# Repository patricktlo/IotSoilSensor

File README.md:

# IotSoilSensor

## This document is under construction!

This project aims to create a cheap LoRa-connected device to measure soil moisture using an embedded capacitive sensor. It also has a temperature sensor (NTC) and an air humidity sensor (HR202).

This project also contains a small simple gateway for LoRa using a LoRa module, a microcontroller and a Raspberry Pi.

## Soil moisture sensor

For the geometry of the sensor I chose a fringing field capacitive sensor because it is well documented and used in academic papers, it was also easy to design it in KiCAD, and easy to simulate in FEMM.

To measure the capacitance a simple RC circuit is used, where R is chosen to achieve a good resolution and measuring range. A comparator (which is inside the STM32L051 microcontroller) is connected to the output of the RC circuit, a simple resistive divider giving Vcc/2 is connected to the other pin of the comparator. 

A square wave is applied to the RC circuit, once the comparator changes state, the code of the MCU gets the value of the timer (the same one used for the square wave generations), with this value it is possible to measure the RC constant and hence the capacitive value. This circuit works quite well, before testing the capacitive sensor with it I tried it with capacitors and the results were really close to the nominal capacitive values ([data here](1_Simulations/Moisture%20sensor/Calibration/test_caps.ods))

### Soil moisture sensor calibration

The gravimetric analysis was used to calibrate our sensor, data can be found [here](1_Simulations/Moisture%20sensor/Calibration/test_gravi.ods). 

## Temperature sensor
The temperature sensor is an NTC thermistor because it's simple, cheap and doesn't depend on battery voltage (like DHT11 and others). The circuit is a simple resistor divider, where the value of the other resistor was chosen by finding the inflection point (using a double derivative, more information on the [HR202 sensor python notebook](1_Simulations/HR202/RH Simulation.ipynb), where I developed the math), you can find the math and some cool graphs on the [NTC sensor python notebook](1_Simulations/NTC/Simulation.ipynb). 

### Temperature sensor calibration
I used the beta-equation for the NTC, [look here for more info](1_Simulations/NTC/Simulation.ipynb).
      
The value of beta was given in the datasheet but I wanted to get a closer value so I calibrated it, see more details [in this spreadsheet](1_Simulations/NTC/NTC_calibration.ods).

## Air humidity sensor
The air humidity sensor was a tough one, it would've been pretty simple and straightforward to use a DHT11, but it would stop working when battery levels got to 3V (so pretty soon considering I'm using two AA batteries). So, I chose the HR202, there's not much about it but it's basically a resistive sensor, the RH value changes with temperature and you have to apply AC to it.

In order to provide AC voltage, I polarized the output at Vcc/2, using a resistor divider (look into the [LTSpice file](1_Simulations/HR202/hr202.asc) or the [KiCAD schematic](2_PCB/schematic.pdf) for more. The value of the resistor in this resistor divider is crucial because its value (or more precisely, the equivalent value of the two) define the output characteristics. To find the value of the resistors the inflex point was used (more info on the [HR202 sensor python notebook](1_Simulations/HR202/RH%20Simulation.ipynb)).

Also, just a quick note, since the input voltage is a square wave controlled by a timer, and we want to gather data from the ADC in sync with the square wave, it is needed to fire the ADC conversion with a timer as well.

### Air humidity calibration

It is difficult to calibrate this sensor, I found that the values in the datasheet weren't close to my results (although it could be some error in the circuit, I later found in another datasheet a somewhat different circuit which could work better). In order to get a fixed relative air humidity, I put the sensor inside a sealed container with a bottle cap of salt and water, that way after a few hours it gets to 75%.
I had an air humidity sensor so I could also use it as a reference. Even though the HR202 wasn't giving out exactly what was written on the datasheet, one could see the output voltage had a correlation with the humidity, so I got two known points, the 75% from the salt-water solution and the ambient RH from the other sensor, and fitted my sensor values to this line. It's far from perfect but it does give an idea of the RH.

## Battery

## LoRa

## STM32L051

## PCB

## Gateway
### Database

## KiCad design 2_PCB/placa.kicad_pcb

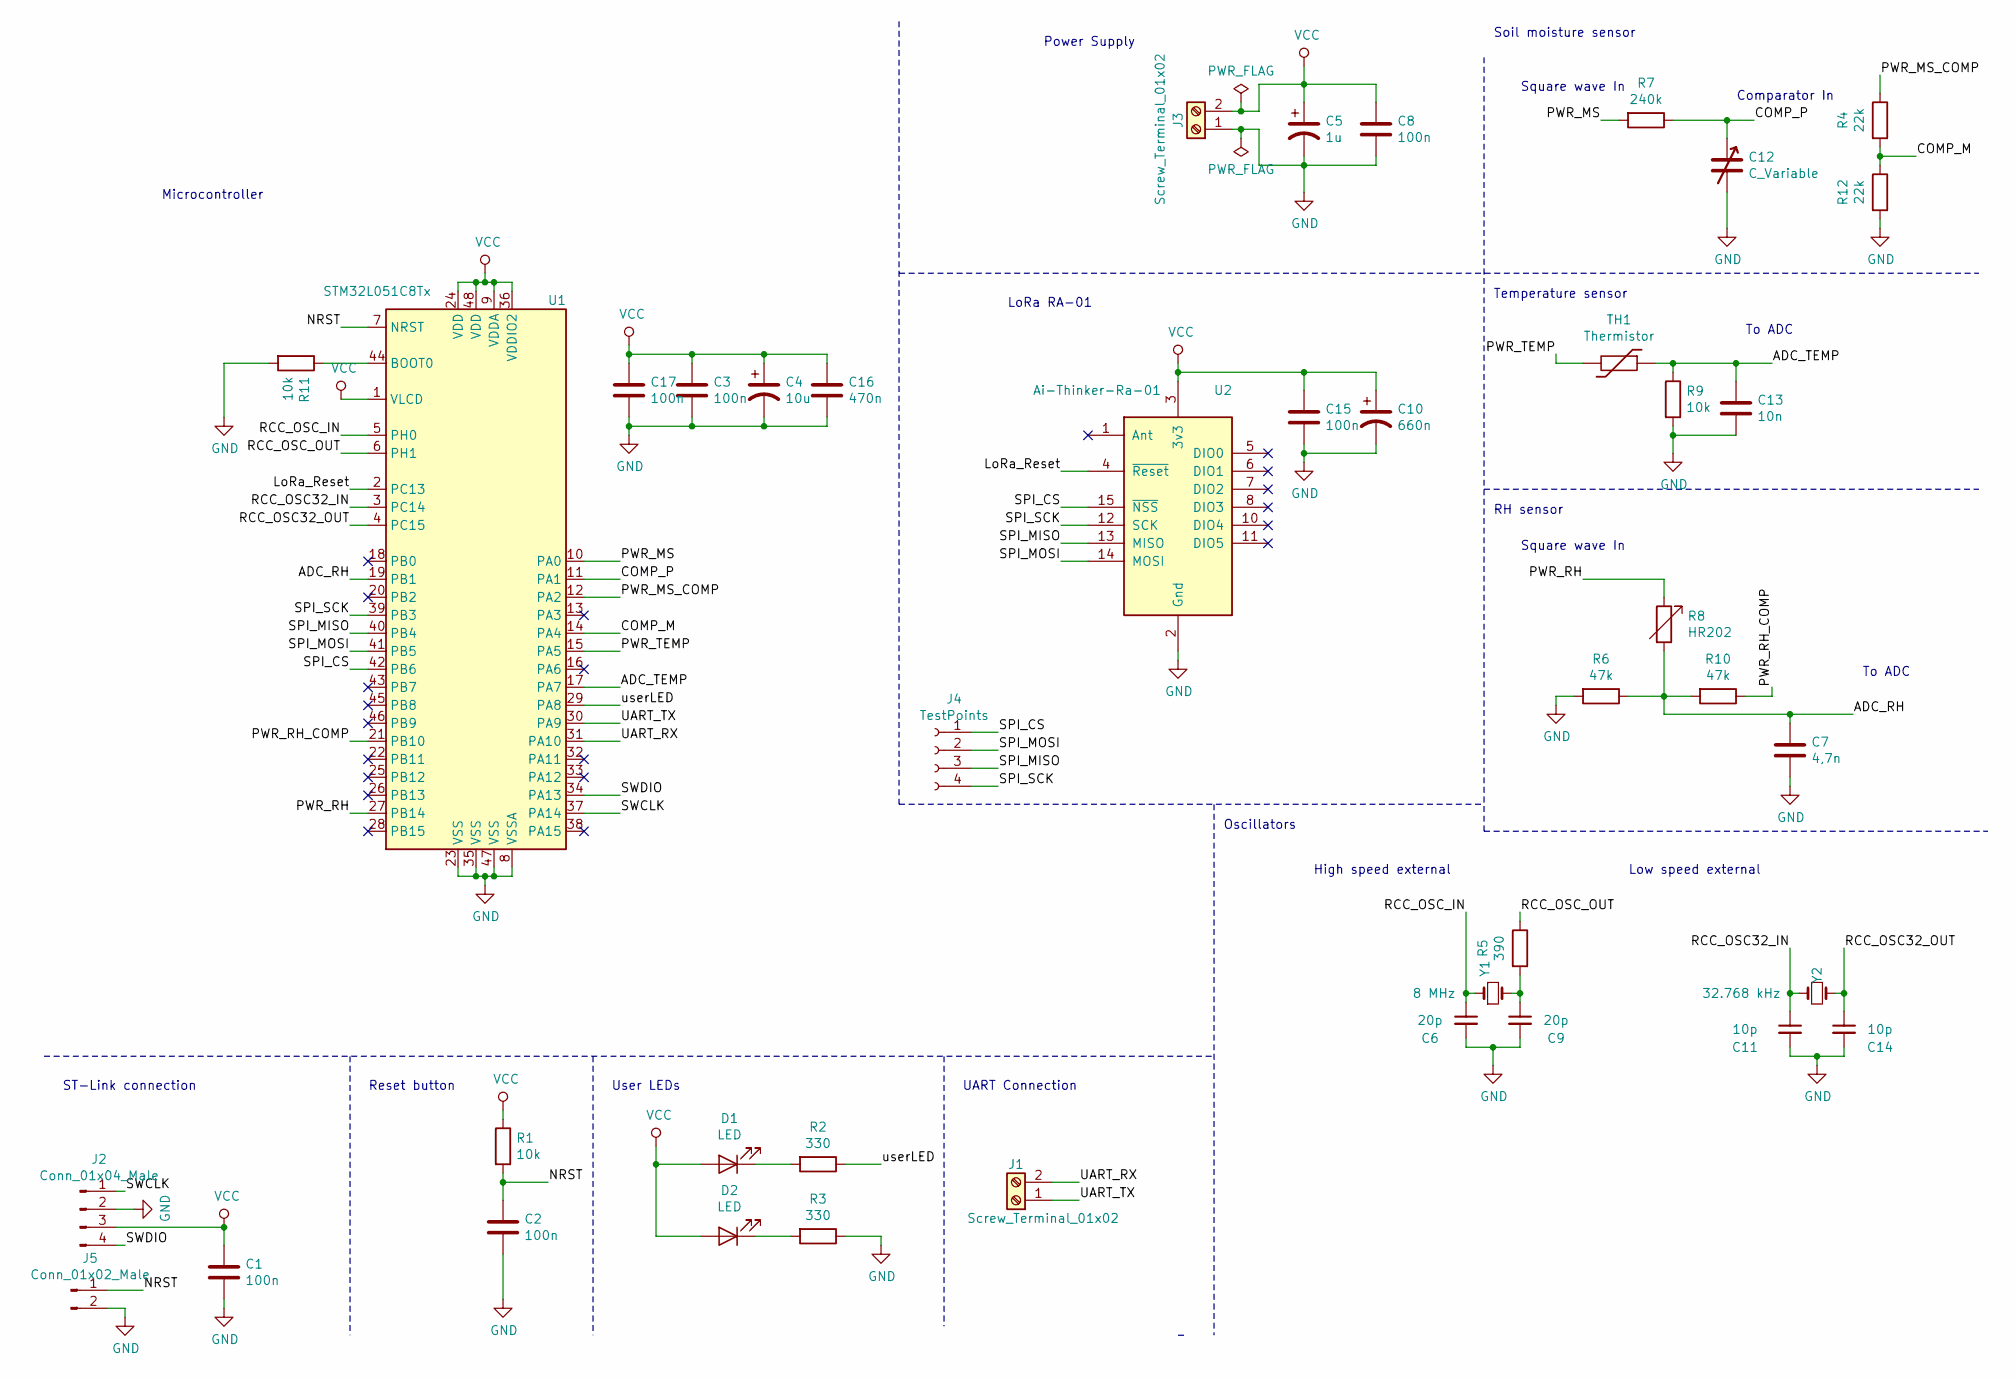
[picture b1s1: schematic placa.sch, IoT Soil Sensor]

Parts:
C1, C2, C3, C8, C15, C17: 100n; C_0805_2012Metric_Pad1.15x1.40mm_HandSolder
C4: 10u; CP_Radial_D5.0mm_P2.50mm
C5: 1u; CP_Radial_D5.0mm_P2.00mm
C6, C9: 20p; C_0805_2012Metric_Pad1.15x1.40mm_HandSolder
C7: 4,7n; C_0805_2012Metric_Pad1.15x1.40mm_HandSolder
C10: 660n; C_0805_2012Metric_Pad1.15x1.40mm_HandSolder
C11, C14: 10p; C_0805_2012Metric_Pad1.15x1.40mm_HandSolder
C12: C_Variable; Moisture Sensor
C13: 10n; C_0805_2012Metric_Pad1.15x1.40mm_HandSolder
C16: 470n; C_0805_2012Metric_Pad1.15x1.40mm_HandSolder
D1, D2: LED; LED_0805_2012Metric_Pad1.15x1.40mm_HandSolder
J1, J3: Screw_Terminal_01x02; PinHeader_1x02_P2.54mm_Vertical
J2: Conn_01x04_Male; PinHeader_1x04_P2.54mm_Vertical
J4: TestPoints; PinHeader_1x04_P2.54mm_Vertical
J5: Conn_01x02_Male; PinHeader_1x02_P2.54mm_Vertical
R1, R9, R11: 10k; R_0805_2012Metric_Pad1.15x1.40mm_HandSolder
R2, R3: 330; R_0805_2012Metric_Pad1.15x1.40mm_HandSolder
R4, R12: 22k; R_0805_2012Metric_Pad1.15x1.40mm_HandSolder
R5: 390; R_0805_2012Metric_Pad1.15x1.40mm_HandSolder
R6, R10: 47k; R_0805_2012Metric_Pad1.15x1.40mm_HandSolder
R7: 240k; R_0805_2012Metric_Pad1.15x1.40mm_HandSolder
R8: HR202; R_Axial_DIN0204_L3.6mm_D1.6mm_P1.90mm_Vertical
TH1: Thermistor; R_Axial_DIN0204_L3.6mm_D1.6mm_P1.90mm_Vertical
U1: STM32L051C8Tx; LQFP-48_7x7mm_P0.5mm
U2: Ai-Thinker-Ra-01; Ai-Thinker-Ra-01-LoRa
Y1: 8 MHz; Crystal_HC49-U_Vertical
Y2: 32.768 kHz; Crystal_Round_D1.0mm_Vertical

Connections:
/ADC_RH: C7.1, R6.1, R8.2, R10.2, U1.19 (PB1)
/ADC_TEMP: C13.1, R9.1, TH1.1, U1.17 (PA7)
/COMP_M: R4.2, R12.1, U1.14 (PA4)
/COMP_P: C12.1, R7.1, U1.11 (PA1)
/LoRa_Reset: U1.2 (PC13), U2.4 (~Reset)
/NRST: C2.1, J5.1, R1.2, U1.7 (NRST)
/PWR_MS: R7.2, U1.10 (PA0)
/PWR_MS_COMP: R4.1, U1.12 (PA2)
/PWR_RH: R8.1, U1.27 (PB14)
/PWR_RH_COMP: R10.1, U1.21 (PB10)
/PWR_TEMP: TH1.2, U1.15 (PA5)
/RCC_OSC32_IN: C11.1, U1.3 (PC14), Y2.2
/RCC_OSC32_OUT: C14.1, U1.4 (PC15), Y2.1
/RCC_OSC_IN: C6.1, U1.5 (PH0), Y1.1
/RCC_OSC_OUT: R5.1, U1.6 (PH1)
/SPI_CS: J4.1, U1.42 (PB6), U2.15 (~NSS)
/SPI_MISO: J4.3, U1.40 (PB4), U2.13 (MISO)
/SPI_MOSI: J4.2, U1.41 (PB5), U2.14 (MOSI)
/SPI_SCK: J4.4, U1.39 (PB3), U2.12 (SCK)
/SWCLK: J2.1, U1.37 (PA14)
/SWDIO: J2.4, U1.34 (PA13)
/UART_RX: J1.2, U1.31 (PA10)
/UART_TX: J1.1, U1.30 (PA9)
/userLED: R2.1, U1.29 (PA8)
GND: C1.2, C2.2, C3.2, C4.2, C5.2, C6.2, C7.2, C8.2, C9.2, C10.2, C11.2, C12.2, C13.2, C14.2, C15.2, C16.2, C17.2, J2.2, J3.1, J5.2, R3.1, R6.2, R9.2, R11.2, R12.2, U1.8 (VSSA), U1.23 (VSS), U1.35 (VSS), U1.47 (VSS), U2.2 (Gnd), U2.9 (Gnd), U2.16 (Gnd)
unnamed: C9.1, R5.2, Y1.2
unnamed: D1.1 (K), R2.2
unnamed: D2.1 (K), R3.2
unnamed: R11.1, U1.44 (BOOT0)
VCC: C1.1, C3.1, C4.1, C5.1, C8.1, C10.1, C15.1, C16.1, C17.1, D1.2 (A), D2.2 (A), J2.3, J3.2, R1.1, U1.1 (VLCD), U1.9 (VDDA), U1.24 (VDD), U1.36 (VDDIO2), U1.48 (VDD), U2.3 (3v3)

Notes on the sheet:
Square wave In
Comparator In
Soil moisture sensor
Temperature sensor
RH sensor
To ADC
Power Supply
ST-Link connection
Reset button
User LEDs
Oscillators
High speed external
Low speed external
UART Connection
LoRa RA-01
Microcontroller

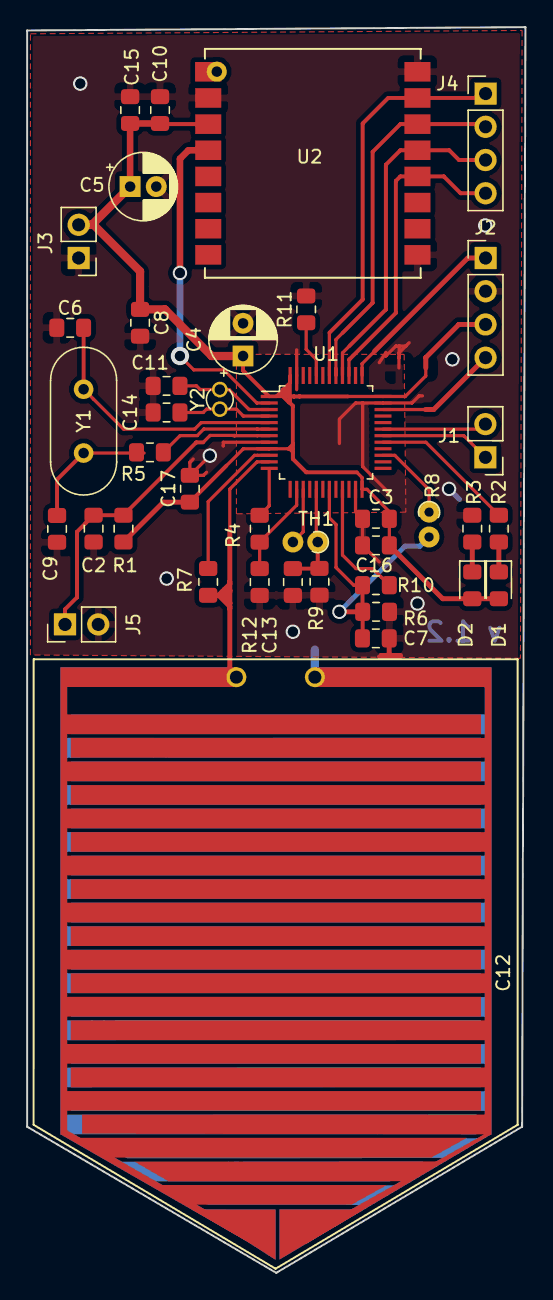
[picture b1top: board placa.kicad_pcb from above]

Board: 2 copper layers, 38.1 x 95.2 mm, 40 parts (0 on the bottom side), 30 nets.

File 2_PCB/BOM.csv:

"Id";"Designator";"Package";"Quantity";"Designation";"Supplier and ref";
1;"C12";"Moisture Sensor";1;"C_Variable";;;
2;"U2";"Ai-Thinker-Ra-01-LoRa";1;"Ai-Thinker-Ra-01";;;
3;"U1";"LQFP-48_7x7mm_P0.5mm";1;"STM32L051C8Tx";;;
4;"C16";"C_0805_2012Metric_Pad1.15x1.40mm_HandSolder";1;"470n";;;
5;"Y2";"Crystal_Round_D1.0mm_Vertical";1;"32.768 kHz";;;
6;"TH1";"R_Axial_DIN0204_L3.6mm_D1.6mm_P1.90mm_Vertical";1;"Thermistor";;;
7;"C1,C2,C3,C8,C15";"C_0805_2012Metric_Pad1.15x1.40mm_HandSolder";5;"100n";;;
8;"C4";"CP_Radial_D5.0mm_P2.50mm";1;"10u";;;
9;"C5";"CP_Radial_D5.0mm_P2.00mm";1;"1u";;;
10;"C6,C9";"C_0805_2012Metric_Pad1.15x1.40mm_HandSolder";2;"20p";;;
11;"C7,C13,C10";"C_0805_2012Metric_Pad1.15x1.40mm_HandSolder";3;"660n";;;
12;"C11,C14";"C_0805_2012Metric_Pad1.15x1.40mm_HandSolder";2;"10p";;;
13;"D1,D2";"LED_0805_2012Metric_Pad1.15x1.40mm_HandSolder";2;"LED";;;
14;"J2";"PinHeader_1x05_P2.54mm_Vertical";1;"Conn_01x05_Male";;;
15;"JP1";"SolderJumper-3_P1.3mm_Bridged12_RoundedPad1.0x1.5mm_NumberLabels";1;"SolderJumper_3_Bridged12";;;
16;"R1,R7,R9";"R_0805_2012Metric_Pad1.15x1.40mm_HandSolder";3;"10k";;;
17;"R2,R3";"R_0805_2012Metric_Pad1.15x1.40mm_HandSolder";2;"330";;;
18;"R4";"R_0805_2012Metric_Pad1.15x1.40mm_HandSolder";1;"100k";;;
19;"R5";"R_0805_2012Metric_Pad1.15x1.40mm_HandSolder";1;"390";;;
20;"R6,R10";"R_0805_2012Metric_Pad1.15x1.40mm_HandSolder";2;"180k";;;
21;"R8";"R_Box_L8.4mm_W2.5mm_P5.08mm";1;"HR202";;;
22;"SW1";"BUTTON_5mm";1;"SW_Push";;;
23;"Y1";"Crystal_HC49-U_Vertical";1;"8 MHz";;;
24;"J1,J3";"PinHeader_1x02_P2.54mm_Vertical";2;"Screw_Terminal_01x02";;;
25;"J4";"PinHeader_1x04_P2.54mm_Vertical";1;"TestPoints";;;
26;"REF**";"Fiducial_classic_Small_CopperTop_Type1";1;"Fiducial_classic_Small_CopperTop_Type1";;;
27;"REF**";"Fiducial_classic_Small_CopperBottom_Type1";1;"Fiducial_classic_Small_CopperBottom_Type1";;;

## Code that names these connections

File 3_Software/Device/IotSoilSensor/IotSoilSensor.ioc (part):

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Mcu.Name=STM32L051C(6-8)Tx
Mcu.Package=LQFP48
Mcu.UserName=STM32L051C8Tx
PA0.GPIOParameters=GPIO_Label
PA0.GPIO_Label=PWR_MS
PA0.Signal=S_TIM2_CH1
PA1.Mode=INP
PA1.Signal=COMP1_INP
PA13.Mode=Serial_Wire
PA13.Signal=SYS_SWDIO
PA14.Mode=Serial_Wire
PA14.Signal=SYS_SWCLK
PA2.GPIOParameters=GPIO_Label
PA2.GPIO_Label=PWR_MS_COMP
PA2.Signal=GPIO_Output
PA4.Mode=INM
PA4.Signal=COMP1_INM
PA5.GPIOParameters=GPIO_Label
PA5.GPIO_Label=PWR_Temp
PA5.Signal=GPIO_Output
PA7.GPIOParameters=GPIO_Label
PA7.GPIO_Label=ADC_TEMP
PA7.Mode=IN7
PA7.Signal=ADC_IN7
PA8.GPIOParameters=GPIO_Label
PA8.GPIO_Label=userLED
PA8.Signal=GPIO_Output
PA9.Signal=GPIO_Output
PB1.GPIOParameters=GPIO_Label
PB1.GPIO_Label=ADC_RH
PB1.Mode=IN9
PB1.Signal=ADC_IN9
PB10.GPIOParameters=GPIO_Label
PB10.GPIO_Label=PWR_RH_COMP
PB10.Signal=GPIO_Output
PB14.GPIOParameters=GPIO_Label
PB14.GPIO_Label=PWR_RH
PB14.Signal=S_TIM21_CH2
PB3.Mode=Full_Duplex_Master
PB3.Signal=SPI1_SCK
PB4.Mode=Full_Duplex_Master
PB4.Signal=SPI1_MISO
PB5.Mode=Full_Duplex_Master
PB5.Signal=SPI1_MOSI
PB6.GPIOParameters=GPIO_Label
PB6.GPIO_Label=LoRa_SS
PB6.Signal=GPIO_Output
PC13.GPIOParameters=GPIO_Label
PC13.GPIO_Label=LoRa_Reset
PC13.Signal=GPIO_Output
PH0-OSC_IN.Mode=HSE-External-Oscillator
PH0-OSC_IN.Signal=RCC_OSC_IN
PH1-OSC_OUT.Mode=HSE-External-Oscillator
PH1-OSC_OUT.Signal=RCC_OSC_OUT
RCC.HSE_VALUE=16000000
RCC.SYSCLKFreq_VALUE=16000000
RCC.SYSCLKSource=RCC_SYSCLKSOURCE_HSE
board=custom

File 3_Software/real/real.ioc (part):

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Mcu.Name=STM32L051C(6-8)Tx
Mcu.Package=LQFP48
Mcu.UserName=STM32L051C8Tx
PA0.Mode=IN0
PA0.Signal=ADC_IN0
PA1.Mode=IN1
PA1.Signal=ADC_IN1
PA11.GPIOParameters=GPIO_Label
PA11.GPIO_Label=userLED
PA11.Signal=GPIO_Output
PA13.Mode=Serial_Wire
PA13.Signal=SYS_SWDIO
PA14.Mode=Serial_Wire
PA14.Signal=SYS_SWCLK
PA2.Mode=IN2
PA2.Signal=ADC_IN2
PA5.Mode=Full_Duplex_Master
PA5.Signal=SPI1_SCK
PA6.Mode=Full_Duplex_Master
PA6.Signal=SPI1_MISO
PA7.Mode=Full_Duplex_Master
PA7.Signal=SPI1_MOSI
PB0.GPIOParameters=GPIO_Label
PB0.GPIO_Label=LoRA_SS
PB0.Signal=GPIO_Output
PB1.GPIOParameters=GPIO_Label
PB1.GPIO_Label=LoRa_Reset
PB1.Signal=GPIO_Output
PC14-OSC32_IN.Mode=LSE-External-Oscillator
PC14-OSC32_IN.Signal=RCC_OSC32_IN
PC15-OSC32_OUT.Mode=LSE-External-Oscillator
PC15-OSC32_OUT.Signal=RCC_OSC32_OUT
PH0-OSC_IN.Mode=HSE-External-Oscillator
PH0-OSC_IN.Signal=RCC_OSC_IN
PH1-OSC_OUT.Mode=HSE-External-Oscillator
PH1-OSC_OUT.Signal=RCC_OSC_OUT
RCC.HSE_VALUE=16000000
RCC.SYSCLKFreq_VALUE=24000000
RCC.SYSCLKSource=RCC_SYSCLKSOURCE_PLLCLK
board=custom

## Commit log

2018-09-11 Updated some sensor values; Finished choice of components; Placements of components in PCB
2018-09-13 Remap SPI pins, reposition components; start routing
2018-09-13 Finished first iteration of PCB
2018-09-17 Created and added capacitive sensor to PCB; Minor changes to the design
2018-09-24 Got LaTeX doc working according to ABNT. Uploaded simulation files of the moisture sensor capacitor. Small changes to the board
2018-09-28 Version 1.01 of PCB (easier for home etch). Chapter one of document
2018-10-03 PCB version 1.1: Easier to home etch and added a BOOT0 PD resistor
2018-10-16 New branch for new HW revision. To add different layout, comparator for MS, change in RH circ
2018-10-19 started unit tests. PCB v1.2 routed
2018-10-26 tested NTC on target hardware. Updated NTC tests. Enabled ADC oversampling for NTC
2018-10-26 Adding new files
2018-11-06 Wrote HR202 app code and drivers, plus MS drivers and (most of) the code. Needs hardware testing. Adapted LoRa drivers, module answers but TX not tested
2018-12-02 Hardware tested all. MS, HR202, Temperature and LoRa module. Added code for the gateway
2019-02-07 Cleaned repo and organized it
2019-02-07 fixed problem with fff
2019-02-07 removed jupyter notebook checkpoints
2019-02-07 .gitignore fix
2019-02-07 deleted some useless files
2019-02-08 Fixed links in README.md
2019-02-08 Uploaded schematic pdf files
2019-02-08 few changes in schematic
